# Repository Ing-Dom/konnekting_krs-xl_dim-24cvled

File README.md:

# KRS-XL_DIM-24CVLED

KRS-XL 24 channel PWM-LED Dimmer (24V DC) 9TE 
- a DIY 24 channel KNX PWM LED dimmer for usage in e-cabinets on DIN rail.

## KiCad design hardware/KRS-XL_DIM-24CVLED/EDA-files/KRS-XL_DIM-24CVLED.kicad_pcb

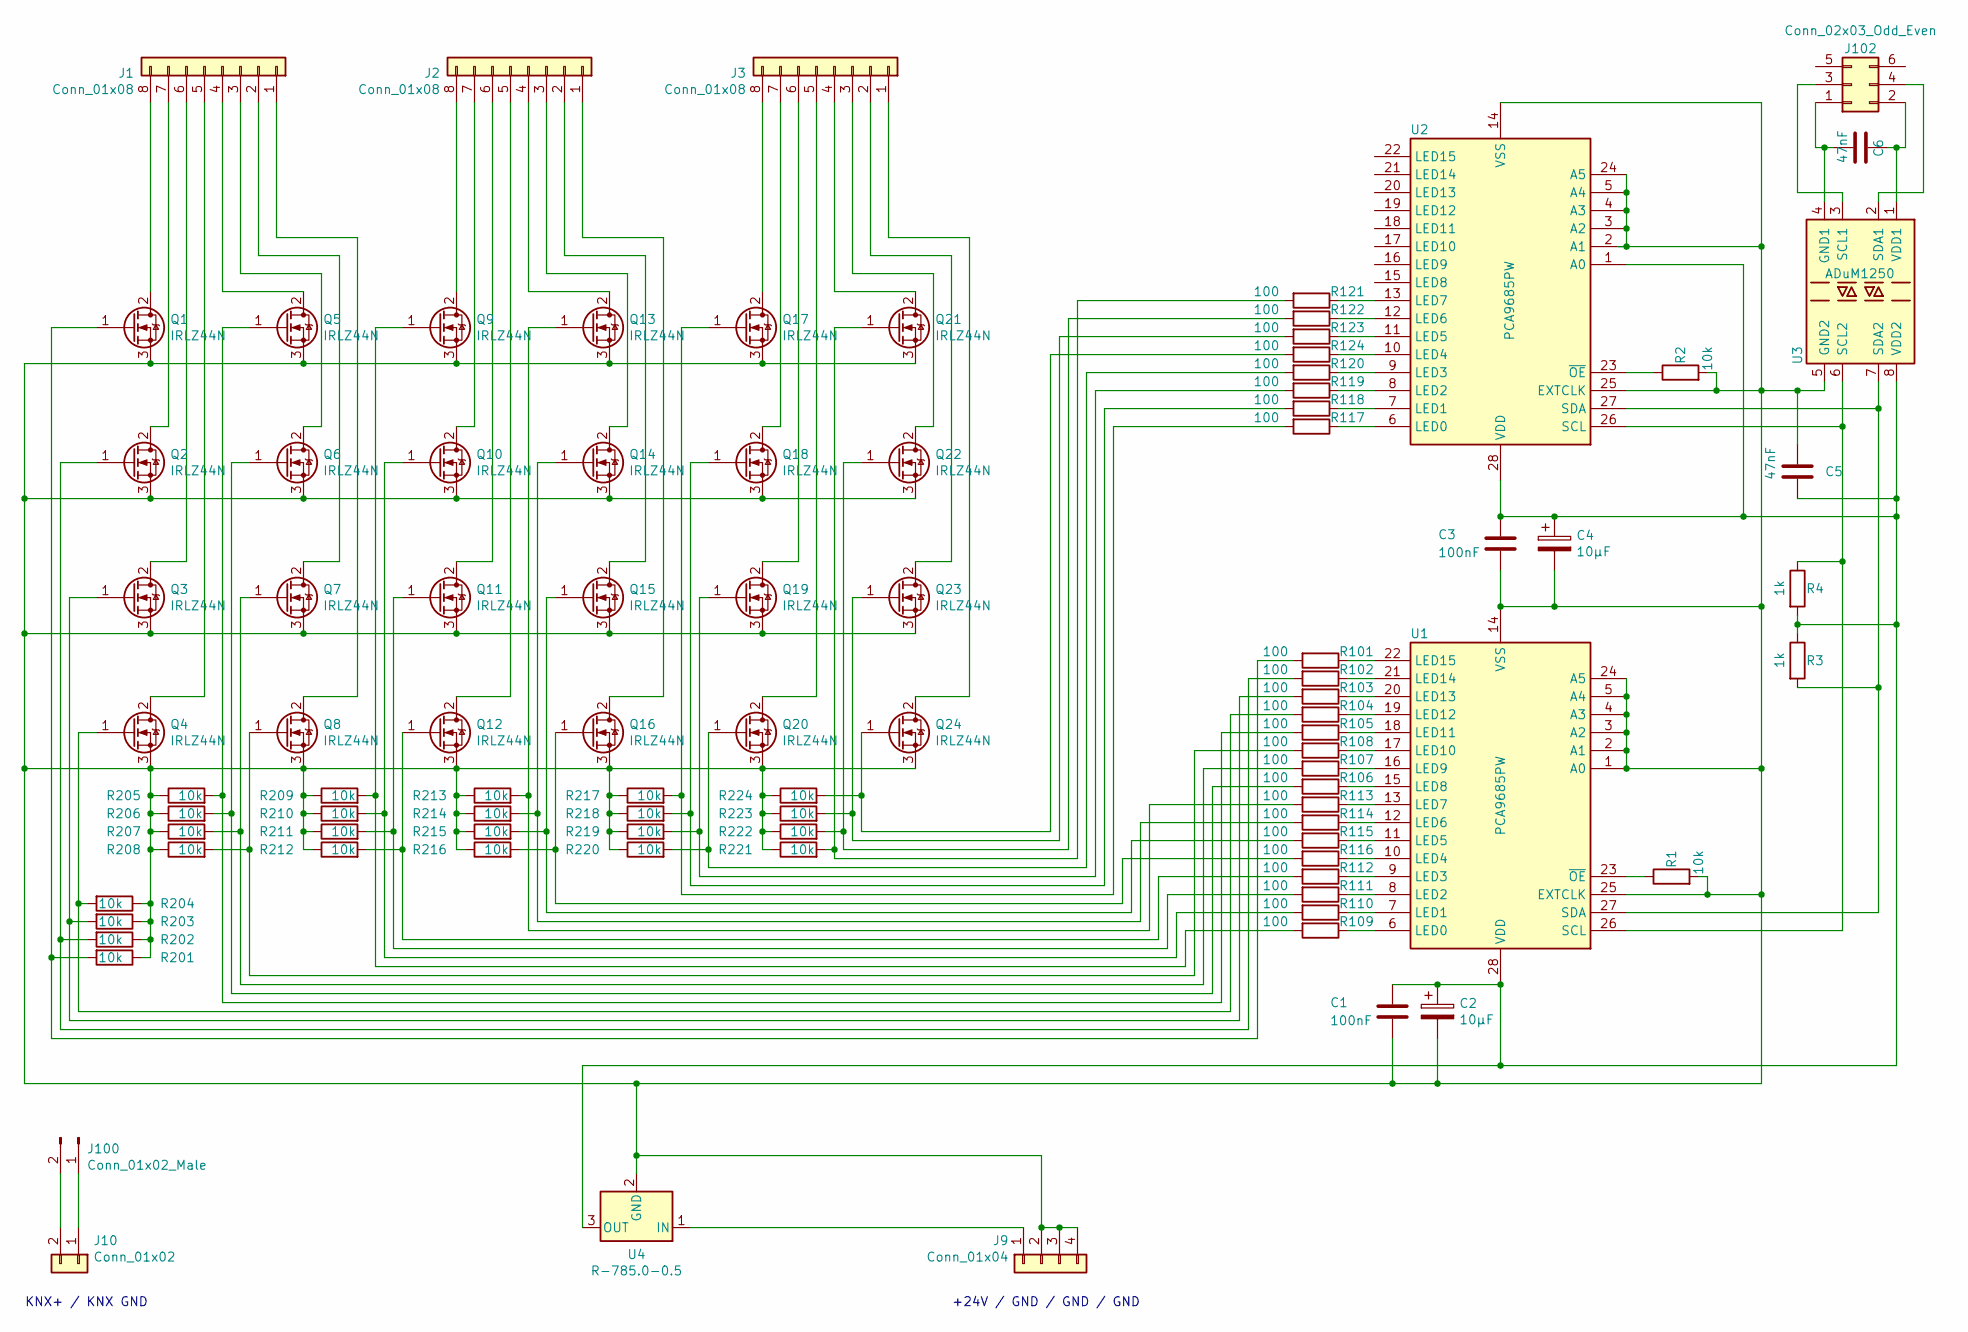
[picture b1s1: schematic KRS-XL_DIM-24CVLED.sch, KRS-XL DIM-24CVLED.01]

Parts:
C1, C3: 100nF; C_1206_3216Metric_Pad1.42x1.75mm_HandSolder
C2, C4: 10µF; CP_Elec_5x5.3
C5, C6: 47nF; C_1206_3216Metric_Pad1.42x1.75mm_HandSolder
J1, J2, J3: Conn_01x08; PhoenixContact_MSTBA_2,5_8-G-5,08_1x08_P5.08mm_Horizontal
J9: Conn_01x04; PhoenixContact_MSTBA_2,5_4-G-5,08_1x04_P5.08mm_Horizontal
J10: Conn_01x02; PhoenixContact_MSTBA_2,5_2-G-5,08_1x02_P5.08mm_Horizontal
J100: Conn_01x02_Male; PinHeader_1x02_P2.54mm_Vertical
J102: Conn_02x03_Odd_Even; IDC-Header_2x03_P2.54mm_Vertical
Q1, Q2, Q3, Q4, Q5, Q6, Q7, Q8, Q9, Q10, Q11, Q12, Q13, Q14, Q15, Q16, Q17, Q18, Q19, Q20, Q21, Q22, Q23, Q24: IRLZ44N; TO-220-3_Horizontal_TabUp_noHole
R1, R2, R201, R202, R203, R204, R205, R206, R207, R208, R209, R210, R211, R212, R213, R214, R215, R216, R217, R218, R219, R220, R221, R222, R223, R224: 10k; R_1206_3216Metric_Pad1.42x1.75mm_HandSolder
R3, R4: 1k; R_1206_3216Metric_Pad1.42x1.75mm_HandSolder
R101, R102, R103, R104, R105, R106, R107, R108, R109, R110, R111, R112, R113, R114, R115, R116, R117, R118, R119, R120, R121, R122, R123, R124: 100; R_1206_3216Metric_Pad1.42x1.75mm_HandSolder
U1, U2: PCA9685PW; TSSOP-28_4.4x9.7mm_P0.65mm
U3: ADuM1250; SOIC-8_3.9x4.9mm_P1.27mm
U4: R-785.0-0.5; SIP-3_P2.54mm_OR_4

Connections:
unnamed: C1.1, C2.1, C3.1, C4.1, C5.2, R3.1, R4.2, U1.28 (VDD), U2.1 (A0), U2.28 (VDD), U3.8 (VDD2), U4.3 (OUT)
unnamed: C1.2, C2.2, C3.2, C4.2, C5.1, J9.2, J9.3, J9.4, Q1.3 (S), Q2.3 (S), Q3.3 (S), Q4.3 (S), Q5.3 (S), Q6.3 (S), Q7.3 (S), Q8.3 (S), Q9.3 (S), Q10.3 (S), Q11.3 (S), Q12.3 (S), Q13.3 (S), Q14.3 (S), Q15.3 (S), Q16.3 (S), Q17.3 (S), Q18.3 (S), Q19.3 (S), Q20.3 (S), Q21.3 (S), Q22.3 (S), Q23.3 (S), Q24.3 (S), R1.2, R2.2, R201.1, R202.1, R203.1, R204.1, R205.1, R206.1, R207.1, R208.1, R209.1, R210.1, R211.1, R212.1, R213.1, R214.1, R215.1, R216.1, R217.1, R218.1, R219.1, R220.1, R221.1, R222.1, R223.1, R224.1, U1.1 (A0), U1.2 (A1), U1.3 (A2), U1.4 (A3), U1.5 (A4), U1.14 (VSS), U1.24 (A5), U1.25 (EXTCLK), U2.2 (A1), U2.3 (A2), U2.4 (A3), U2.5 (A4), U2.14 (VSS), U2.24 (A5), U2.25 (EXTCLK), U3.5 (GND2), U4.2 (GND)
unnamed: C6.1, J102.2, U3.1 (VDD1)
unnamed: C6.2, J102.1, U3.4 (GND1)
unnamed: J1.1, Q8.2 (D)
unnamed: J1.2, Q7.2 (D)
unnamed: J1.3, Q6.2 (D)
unnamed: J1.4, Q5.2 (D)
unnamed: J1.5, Q4.2 (D)
unnamed: J1.6, Q3.2 (D)
unnamed: J1.7, Q2.2 (D)
unnamed: J1.8, Q1.2 (D)
unnamed: J2.1, Q16.2 (D)
unnamed: J2.2, Q15.2 (D)
unnamed: J2.3, Q14.2 (D)
unnamed: J2.4, Q13.2 (D)
unnamed: J2.5, Q12.2 (D)
unnamed: J2.6, Q11.2 (D)
unnamed: J2.7, Q10.2 (D)
unnamed: J2.8, Q9.2 (D)
unnamed: J3.1, Q24.2 (D)
unnamed: J3.2, Q23.2 (D)
unnamed: J3.3, Q22.2 (D)
unnamed: J3.4, Q21.2 (D)
unnamed: J3.5, Q20.2 (D)
unnamed: J3.6, Q19.2 (D)
unnamed: J3.7, Q18.2 (D)
unnamed: J3.8, Q17.2 (D)
unnamed: J9.1, U4.1 (IN)
unnamed: J10.1, J100.1
unnamed: J10.2, J100.2
unnamed: J102.3, U3.3 (SCL1)
unnamed: J102.4, U3.2 (SDA1)
unnamed: Q1.1 (G), R101.2, R201.2
unnamed: Q2.1 (G), R102.2, R202.2
unnamed: Q3.1 (G), R103.2, R203.2
unnamed: Q4.1 (G), R104.2, R204.2
unnamed: Q5.1 (G), R105.2, R205.2
unnamed: Q6.1 (G), R106.2, R206.2
unnamed: Q7.1 (G), R107.2, R207.2
unnamed: Q8.1 (G), R108.2, R208.2
unnamed: Q9.1 (G), R109.2, R209.2
unnamed: Q10.1 (G), R110.2, R210.2
unnamed: Q11.1 (G), R111.2, R211.2
unnamed: Q12.1 (G), R112.2, R212.2
unnamed: Q13.1 (G), R113.2, R213.2
unnamed: Q14.1 (G), R114.2, R214.2
unnamed: Q15.1 (G), R115.2, R215.2
unnamed: Q16.1 (G), R116.2, R216.2
unnamed: Q17.1 (G), R117.2, R217.2
unnamed: Q18.1 (G), R118.2, R218.2
unnamed: Q19.1 (G), R119.2, R219.2
unnamed: Q20.1 (G), R120.2, R220.2
unnamed: Q21.1 (G), R121.2, R221.2
unnamed: Q22.1 (G), R122.2, R222.2
unnamed: Q23.1 (G), R123.2, R223.2
unnamed: Q24.1 (G), R124.2, R224.2
unnamed: R1.1, U1.23 (~OE)
unnamed: R2.1, U2.23 (~OE)
unnamed: R3.2, U1.27 (SDA), U2.27 (SDA), U3.7 (SDA2)
unnamed: R4.1, U1.26 (SCL), U2.26 (SCL), U3.6 (SCL2)
unnamed: R101.1, U1.22 (LED15)
unnamed: R102.1, U1.21 (LED14)
unnamed: R103.1, U1.20 (LED13)
unnamed: R104.1, U1.19 (LED12)
unnamed: R105.1, U1.18 (LED11)
unnamed: R106.1, U1.15 (LED8)
unnamed: R107.1, U1.16 (LED9)
unnamed: R108.1, U1.17 (LED10)
unnamed: R109.1, U1.6 (LED0)
unnamed: R110.1, U1.7 (LED1)
unnamed: R111.1, U1.8 (LED2)
unnamed: R112.1, U1.9 (LED3)
unnamed: R113.1, U1.13 (LED7)
unnamed: R114.1, U1.12 (LED6)
unnamed: R115.1, U1.11 (LED5)
unnamed: R116.1, U1.10 (LED4)
unnamed: R117.1, U2.6 (LED0)
unnamed: R118.1, U2.7 (LED1)
unnamed: R119.1, U2.8 (LED2)
unnamed: R120.1, U2.9 (LED3)
unnamed: R121.1, U2.13 (LED7)
unnamed: R122.1, U2.12 (LED6)
unnamed: R123.1, U2.11 (LED5)
unnamed: R124.1, U2.10 (LED4)

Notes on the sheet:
+24V / GND / GND / GND
KNX+ / KNX GND

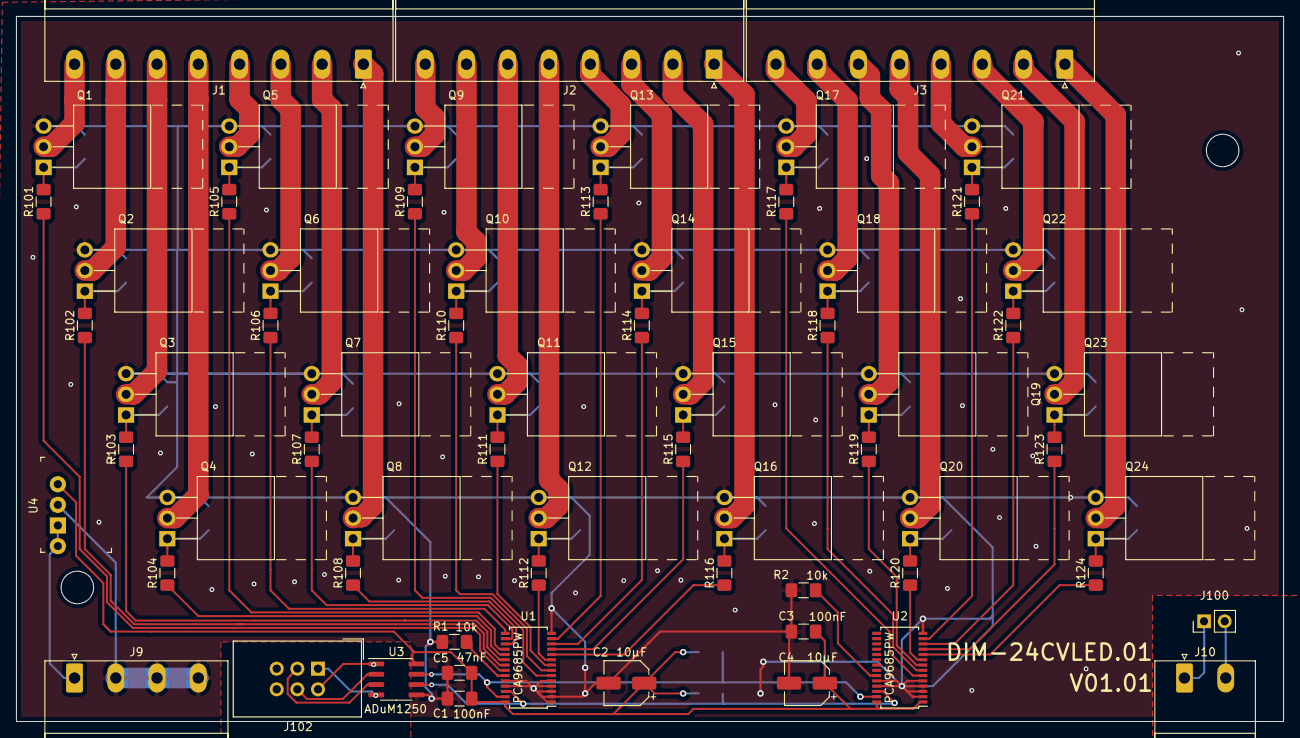
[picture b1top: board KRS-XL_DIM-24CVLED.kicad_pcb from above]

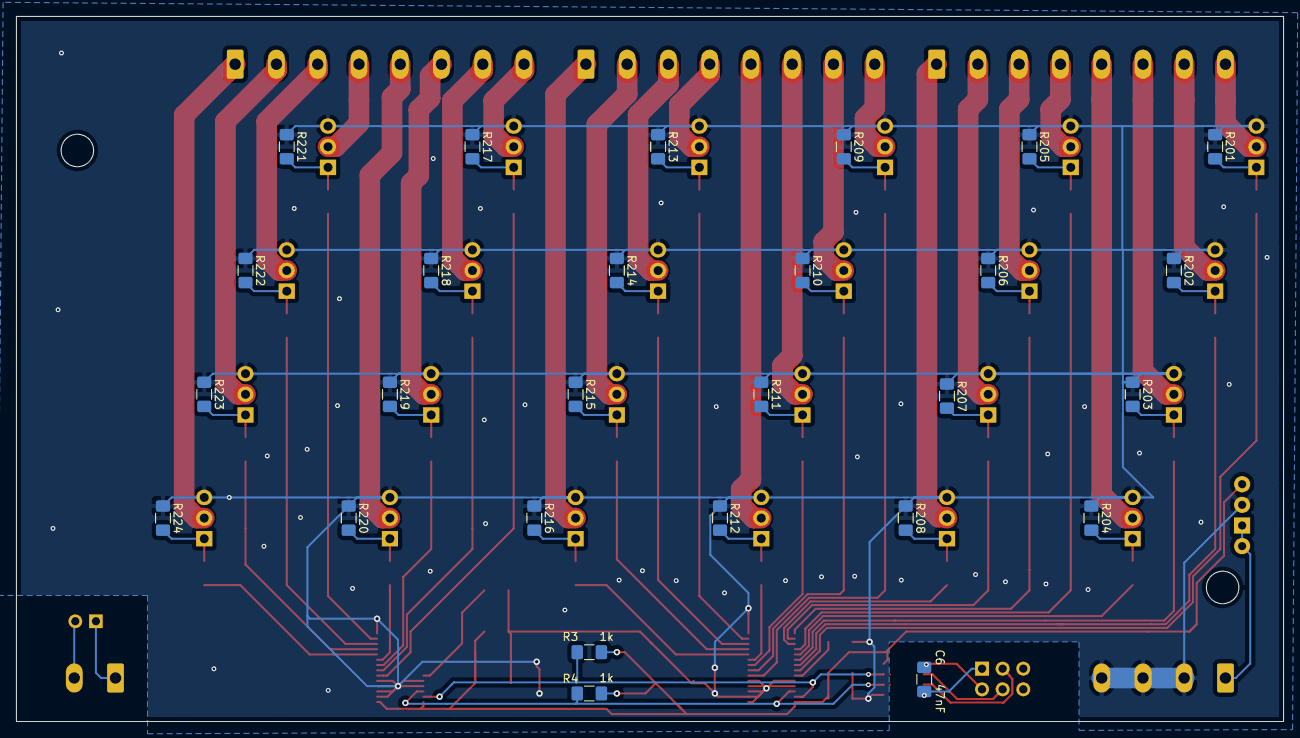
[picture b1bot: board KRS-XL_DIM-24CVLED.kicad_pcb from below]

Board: 2 copper layers, 156.0 x 86.8 mm, 93 parts (27 on the bottom side), 85 nets.

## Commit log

2021-02-06 Add LICENSE
2021-02-09 moved from modular_led_dimmer repo
2021-02-09 rename schematic
2021-02-11 improved BOM
2021-03-02 fixed bug, wrong COMOBJ ident assigned (channel x mixed up)
